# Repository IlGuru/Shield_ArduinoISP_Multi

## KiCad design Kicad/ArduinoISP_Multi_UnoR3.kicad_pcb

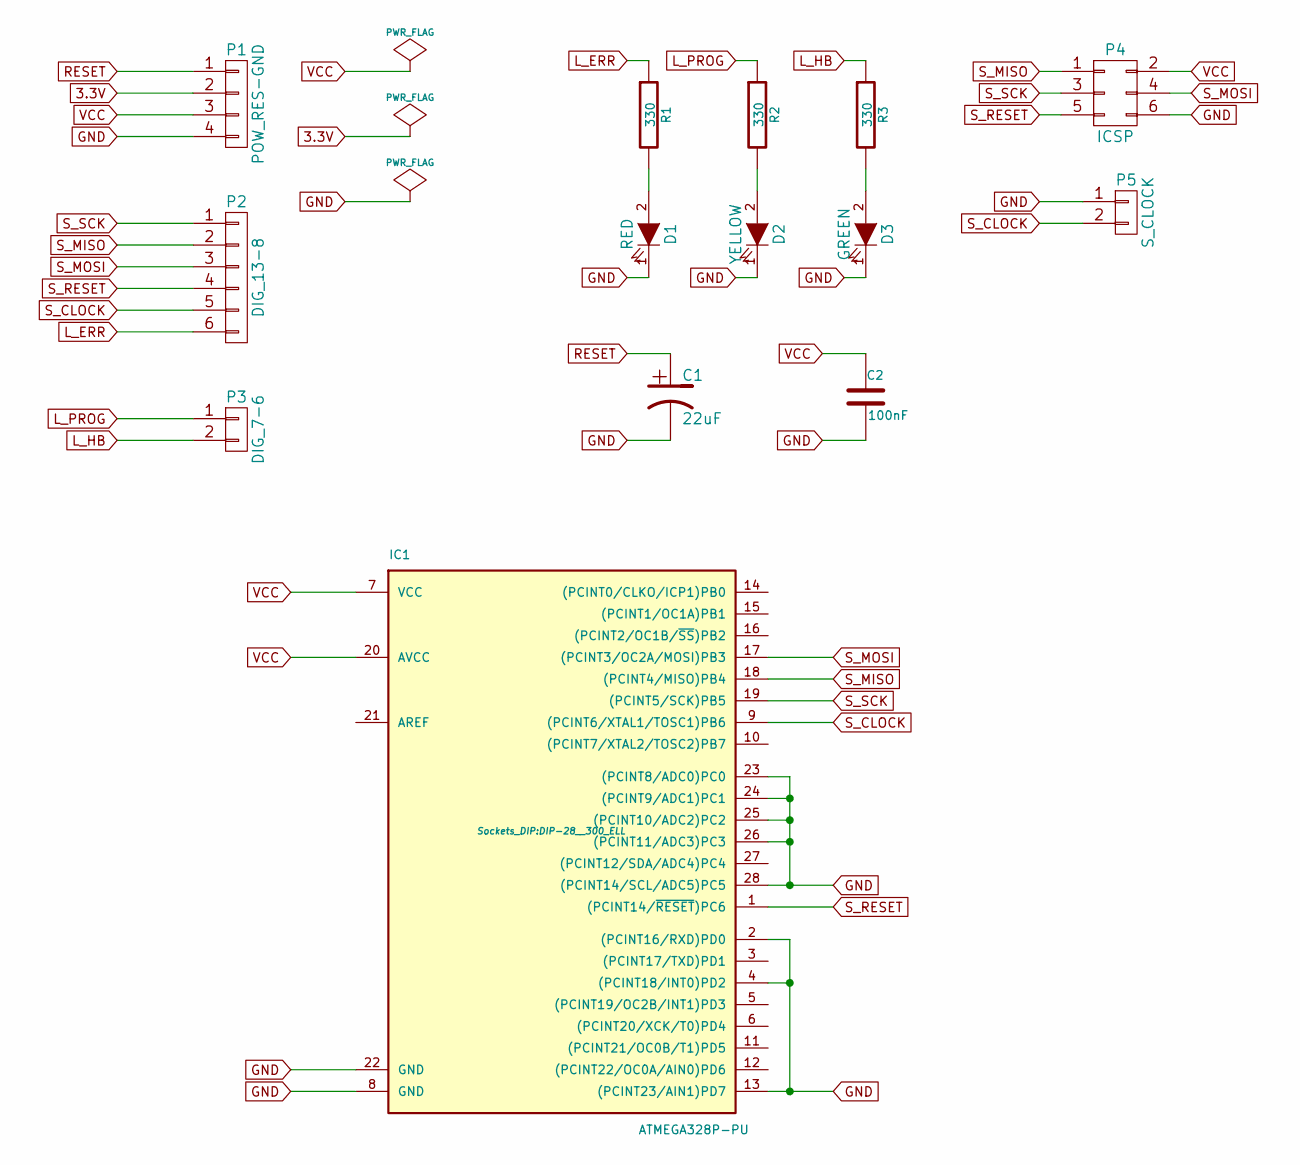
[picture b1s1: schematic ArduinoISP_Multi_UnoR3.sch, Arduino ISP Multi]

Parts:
C1: 22uF; C_Radial_D5_L11_P2.5
C2: 100nF; C_Rect_L7_W2.5_P5
D1: RED; LED-3MM
D2: YELLOW; LED-3MM
D3: GREEN; LED-3MM
IC1: ATMEGA328P-PU; DIP-28__300_ELL
P1: POW_RES-GND; Pin_Header_Straight_1x04
P2: DIG_13-8; Pin_Header_Straight_1x06
P3: DIG_7-6; Pin_Header_Straight_1x02
P4: ICSP; Pin_Header_Straight_2x03
P5: S_CLOCK; Pin_Header_Straight_2x01
R1, R2, R3: 330; Resistor_Horizontal_RM10mm

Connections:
3.3V: P1.2
GND: C1.2, C2.2, D1.1 (K), D2.1 (K), D3.1 (K), IC1.2 ((PCINT16/RXD)PD0), IC1.4 ((PCINT18/INT0)PD2), IC1.8 (GND), IC1.13 ((PCINT23/AIN1)PD7), IC1.22 (GND), IC1.23 ((PCINT8/ADC0)PC0), IC1.24 ((PCINT9/ADC1)PC1), IC1.25 ((PCINT10/ADC2)PC2), IC1.26 ((PCINT11/ADC3)PC3), IC1.28 ((PCINT14/SCL/ADC5)PC5), P1.4, P4.6, P5.1
L_ERR: P2.6, R1.1
L_HB: P3.2, R3.1
L_PROG: P3.1, R2.1
unnamed: D1.2 (A), R1.2
unnamed: D2.2 (A), R2.2
unnamed: D3.2 (A), R3.2
RESET: C1.1, P1.1
S_CLOCK: IC1.9 ((PCINT6/XTAL1/TOSC1)PB6), P2.5, P5.2
S_MISO: IC1.18 ((PCINT4/MISO)PB4), P2.2, P4.1
S_MOSI: IC1.17 ((PCINT3/OC2A/MOSI)PB3), P2.3, P4.4
S_RESET: IC1.1 ((PCINT14/~RESET~)PC6), P2.4, P4.5
S_SCK: IC1.19 ((PCINT5/SCK)PB5), P2.1, P4.3
VCC: C2.1, IC1.7 (VCC), IC1.20 (AVCC), P1.3, P4.2

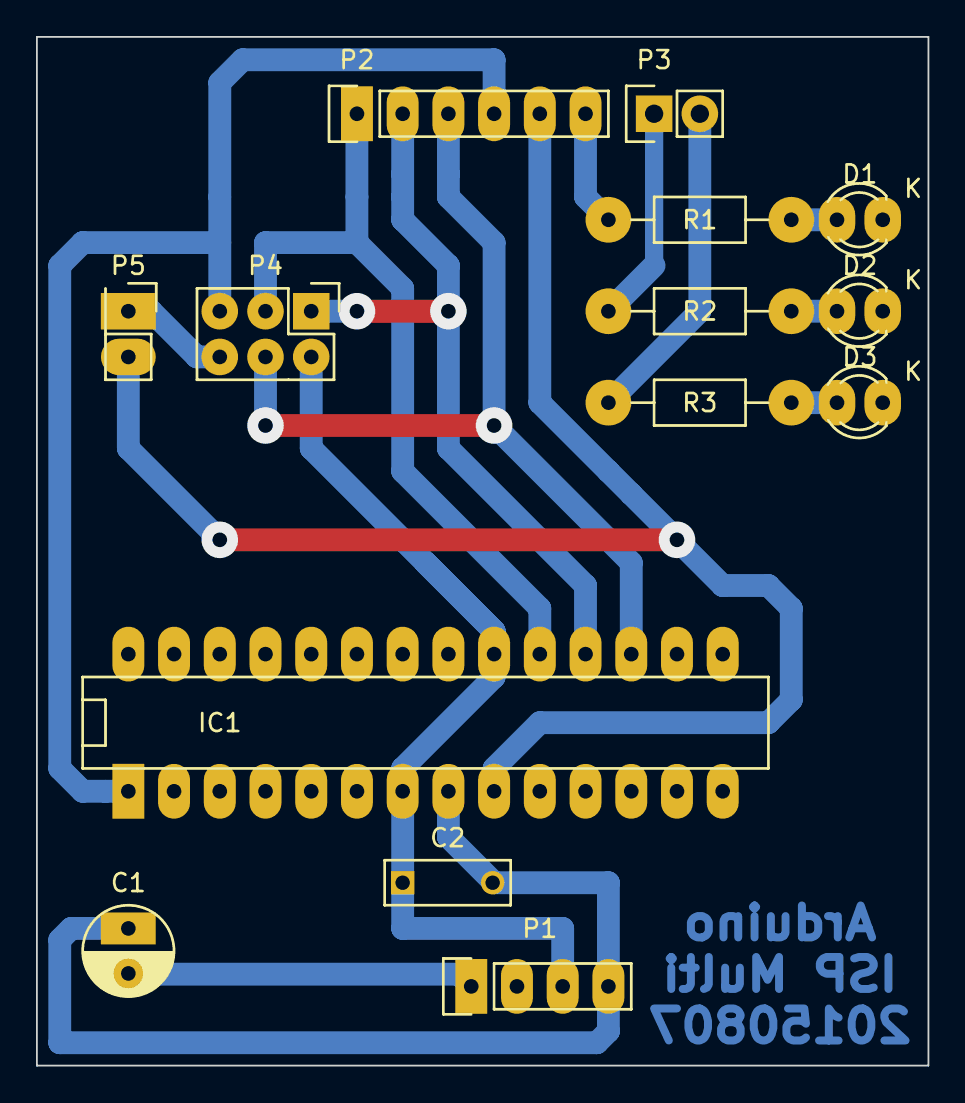
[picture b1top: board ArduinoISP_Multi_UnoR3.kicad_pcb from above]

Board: 2 copper layers, 49.5 x 57.2 mm, 14 parts (0 on the bottom side), 14 nets.

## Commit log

2015-09-07 :neckbeard: Added .gitattributes & .gitignore files
2015-09-07 Creazione repo
2015-09-11 Materiale blog Electroyou
2015-09-13 Schema elettrico e Testo per blog Electroyou
